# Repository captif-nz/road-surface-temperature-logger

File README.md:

# Road surface temperature logger

The road surface temperature logger has been designed as a low-cost unit to support various road surfacing trials. The logger utilises a Pycom microcontroller with screw terminals for upto four DS18B20 temperature probes. Inputs are also provided for a rain gauge, anemometer and light sensor, if needed.

The Pycom microcontroller provides for easier development of the onboard software (in Python), along with built-in cellular and/or LoRa/SigFox connectivity. 

## Parts list

### Custom parts (see sections below)

- PCB
- Enclosure mount

### PCB components
- [Pycom FiPy](https://pycom.io/product/fipy/) or [LoPy4](https://pycom.io/product/lopy4) (no cellular)
- [Lithium battery solar charge controller](https://www.adafruit.com/product/390)
- 2x [JST-PH socket](https://nz.rs-online.com/web/p/products/8201422/)
- 2x [Tactile switch](https://nz.rs-online.com/web/p/products/4791413/)
- 2x [100k Ohm resistor](https://nz.rs-online.com/web/p/through-hole-fixed-resistors/7550704/)
- 1x [4.7k Ohm resistor](https://nz.rs-online.com/web/p/through-hole-fixed-resistors/7077726/)
- 1x [220 Ohm resistor](https://nz.rs-online.com/web/p/through-hole-fixed-resistors/7077612/)
- 2x [14-way PCB socket (single row, 2.54mm)](https://nz.rs-online.com/web/p/products/1981500/)
- 1x [6-way PCB socket (single row, 2.54mm)](https://nz.rs-online.com/web/p/pcb-sockets/1981494)
- 3x [2-way PCB header (single row, 2.54mm)](https://nz.rs-online.com/web/p/pcb-headers/1802111/)
- 3x [6-way terminal block (2.54mm)](https://nz.rs-online.com/web/p/products/1918717/)
- 1x [2-way terminal block (2.54mm)](https://nz.rs-online.com/web/p/pcb-terminal-blocks/1919055/)

### Logger hardware
- [Enclosure with polycarbonate cover](https://www.digikey.co.nz/product-detail/en/bud-industries/PN-1325-CMB/377-1894-ND/2674158)
- [2.5W solar panel](https://www.seeedstudio.com/2-5W-Solar-Panel-116X160.html)
- 3.7V lithium battery (~13.8 Ah with built-in protection)
- [DS18B20 temperature probes](https://nz.rs-online.com/web/p/temperature-humidity-sensor-ics/1901709/)
- 3-core sensor wire (temperature probe extension)
- [6.4mm heat shrink](https://nz.rs-online.com/web/p/heat-shrink-cold-shrink-sleeves/0397821) (temperature probe encapsulation)
- [*DAVIS rain collector #6466M*](https://scientificsales.co.nz/davis-6466m-aerocone-rain-collector-pole-mount-0.2mm/) (optional)
- [*DAVIS anemometer #6410*](https://scientificsales.co.nz/davis-6410-anemometer-for-vantage-pro/) (optional)

### Programming hardware
- [PyCom Expansion board](https://pycom.io/product/expansion-board-3-0/) OR
- [Serial programmer](https://nz.rs-online.com/web/p/communication-wireless-development-tools/1346453/)

### Mounting system
- Pole and socket
- U-bolts

## PCB

The printed circuit board manufacturing files can be found in [assembley_files.zip](assembly_files.zip). There are a number of low-cost options available for getting these manufactured.

## Enclosure mount

Models of the enclosure mounting plate and solar panel frame can be found in [enclosure_mount.zip](enclosure_mount.zip). These are designed for the enclosure, solar panel and PCB listed in the parts section above. The enclosure mount parts should be 3D printed out of ABS plastic.

## Licence

MIT

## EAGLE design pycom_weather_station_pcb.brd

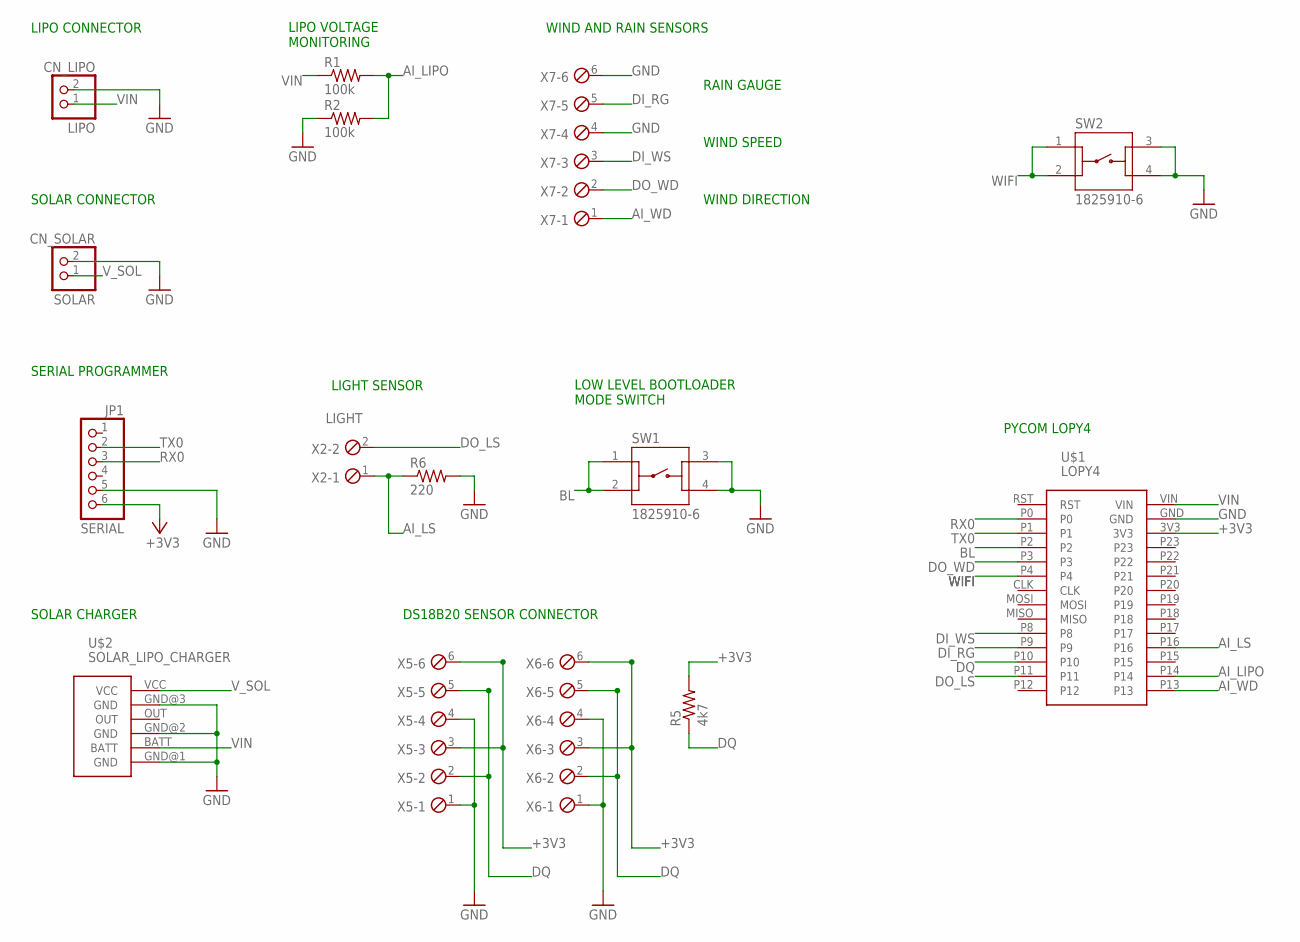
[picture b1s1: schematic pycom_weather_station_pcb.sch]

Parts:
CN_LIPO: LIPO; JST-PH-2-THM
CN_SOLAR: SOLAR; JST-PH-2-THM
JP1: SERIAL; 1X06-CLEANBIG
R1, R2: 100k; 0204/7
R5: 4k7; 0204/7
R6: 220; 0204/7
SW1, SW2: 1825910-6; SW_1825910-6-4
U$1: LOPY4
U$2: SOLAR_LIPO_CHARGER
X2: LIGHT; 2POL254
X5, X6, X7: MPT6; 6POL254

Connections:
+3V3: JP1.6, R5.2, U$1.3V3, X5.3, X5.6, X6.3, X6.6
AI_LIPO: R1.2, R2.2, U$1.P14
AI_LS: R6.1, U$1.P16, X2.1
AI_WD: U$1.P13, X7.1
BL: SW1.1, SW1.2, U$1.P2
DI_RG: U$1.P9, X7.5
DI_WS: U$1.P8, X7.3
DO_LS: U$1.P11, X2.2
DO_WD: U$1.P3, X7.2
DQ: R5.1, U$1.P10, X5.2, X5.5, X6.2, X6.5
GND: CN_LIPO.2 (1), CN_SOLAR.2 (1), JP1.5, R2.1, R6.2, SW1.3, SW1.4, SW2.3, SW2.4, U$1.GND, U$2.GND@1 (GND), U$2.GND@2 (GND), U$2.GND@3 (GND), X5.1, X5.4, X6.1, X6.4, X7.4, X7.6
RX0: JP1.3, U$1.P0
TX0: JP1.2, U$1.P1
VIN: CN_LIPO.1 (2), R1.1, U$1.VIN, U$2.BATT
V_SOL: CN_SOLAR.1 (2), U$2.VCC
WIFI: SW2.1, SW2.2, U$1.P4

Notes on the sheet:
LIPO CONNECTOR
SOLAR CONNECTOR
SERIAL PROGRAMMER
SOLAR CHARGER
LIPO VOLTAGE MONITORING
DS18B20 SENSOR CONNECTOR
LIGHT SENSOR
WIND DIRECTION
WIND SPEED
RAIN GAUGE
WIND AND RAIN SENSORS
LOW LEVEL BOOTLOADER MODE SWITCH
PYCOM LOPY4

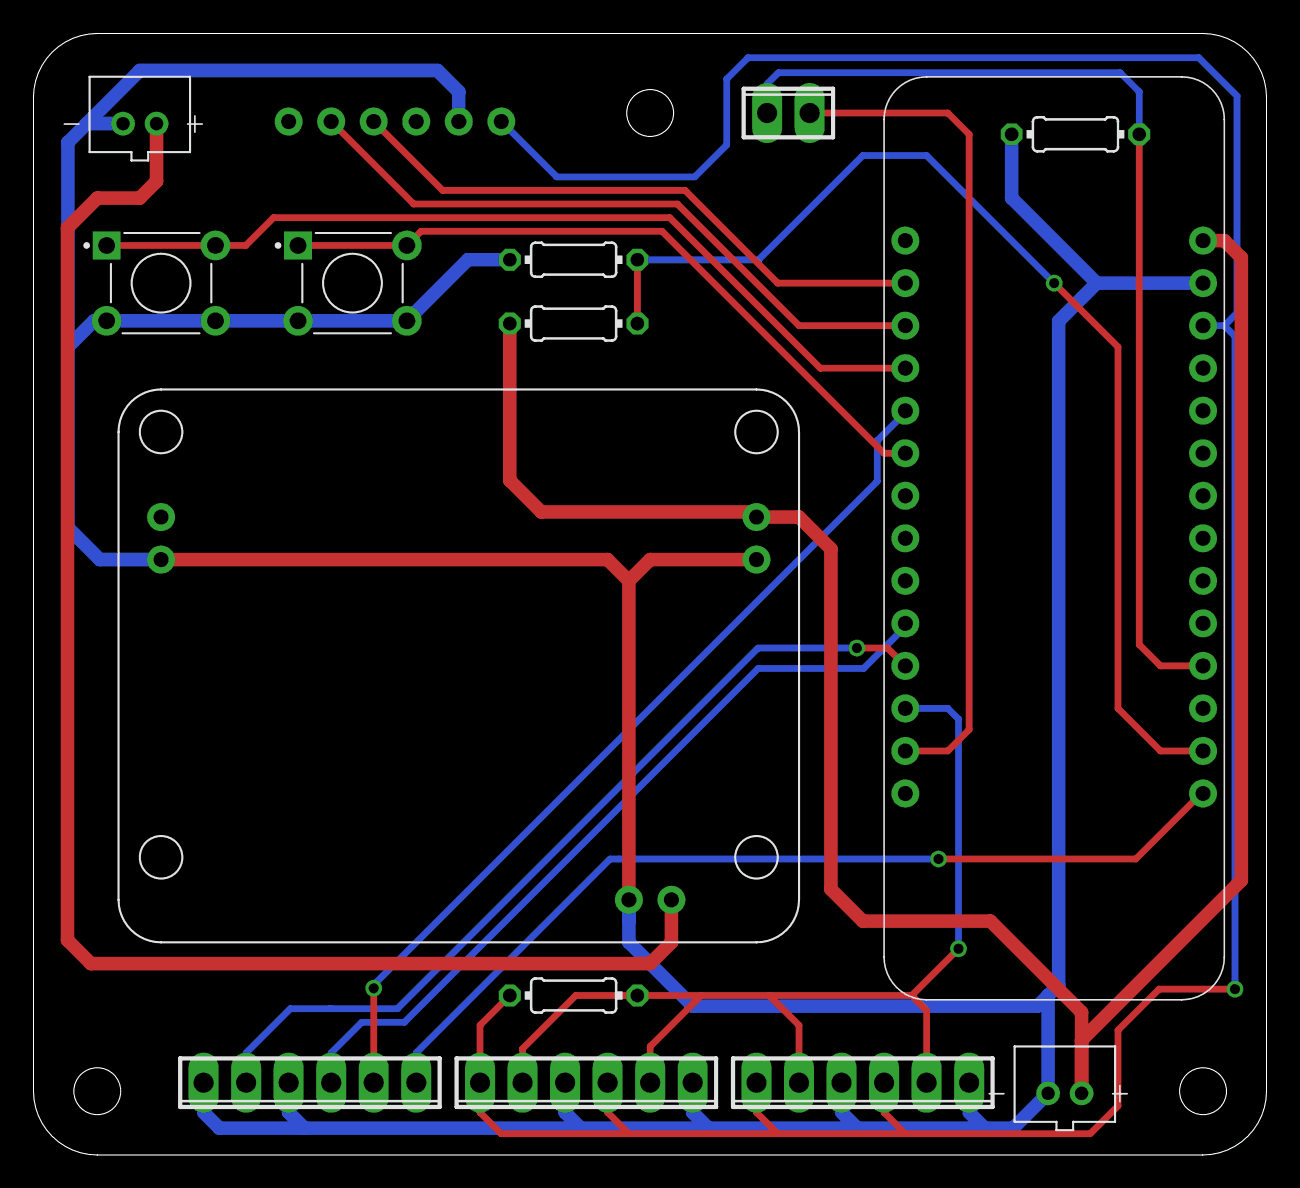
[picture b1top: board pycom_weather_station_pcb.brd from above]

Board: 2 copper layers, 73.6 x 67.0 mm, 15 parts (0 on the bottom side), 16 nets.

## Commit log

2021-03-12 Create LICENCE
2021-03-12 Add pcb image
2021-06-01 add enclosure stl models
2021-06-01 ignore folders
2021-06-01 update pcb design
2021-06-01 add solar panel frame
